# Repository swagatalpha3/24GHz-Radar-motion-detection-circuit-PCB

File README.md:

# 24GHz-Radar-motion-detection-circuit-PCB
PCB design using KiCAD

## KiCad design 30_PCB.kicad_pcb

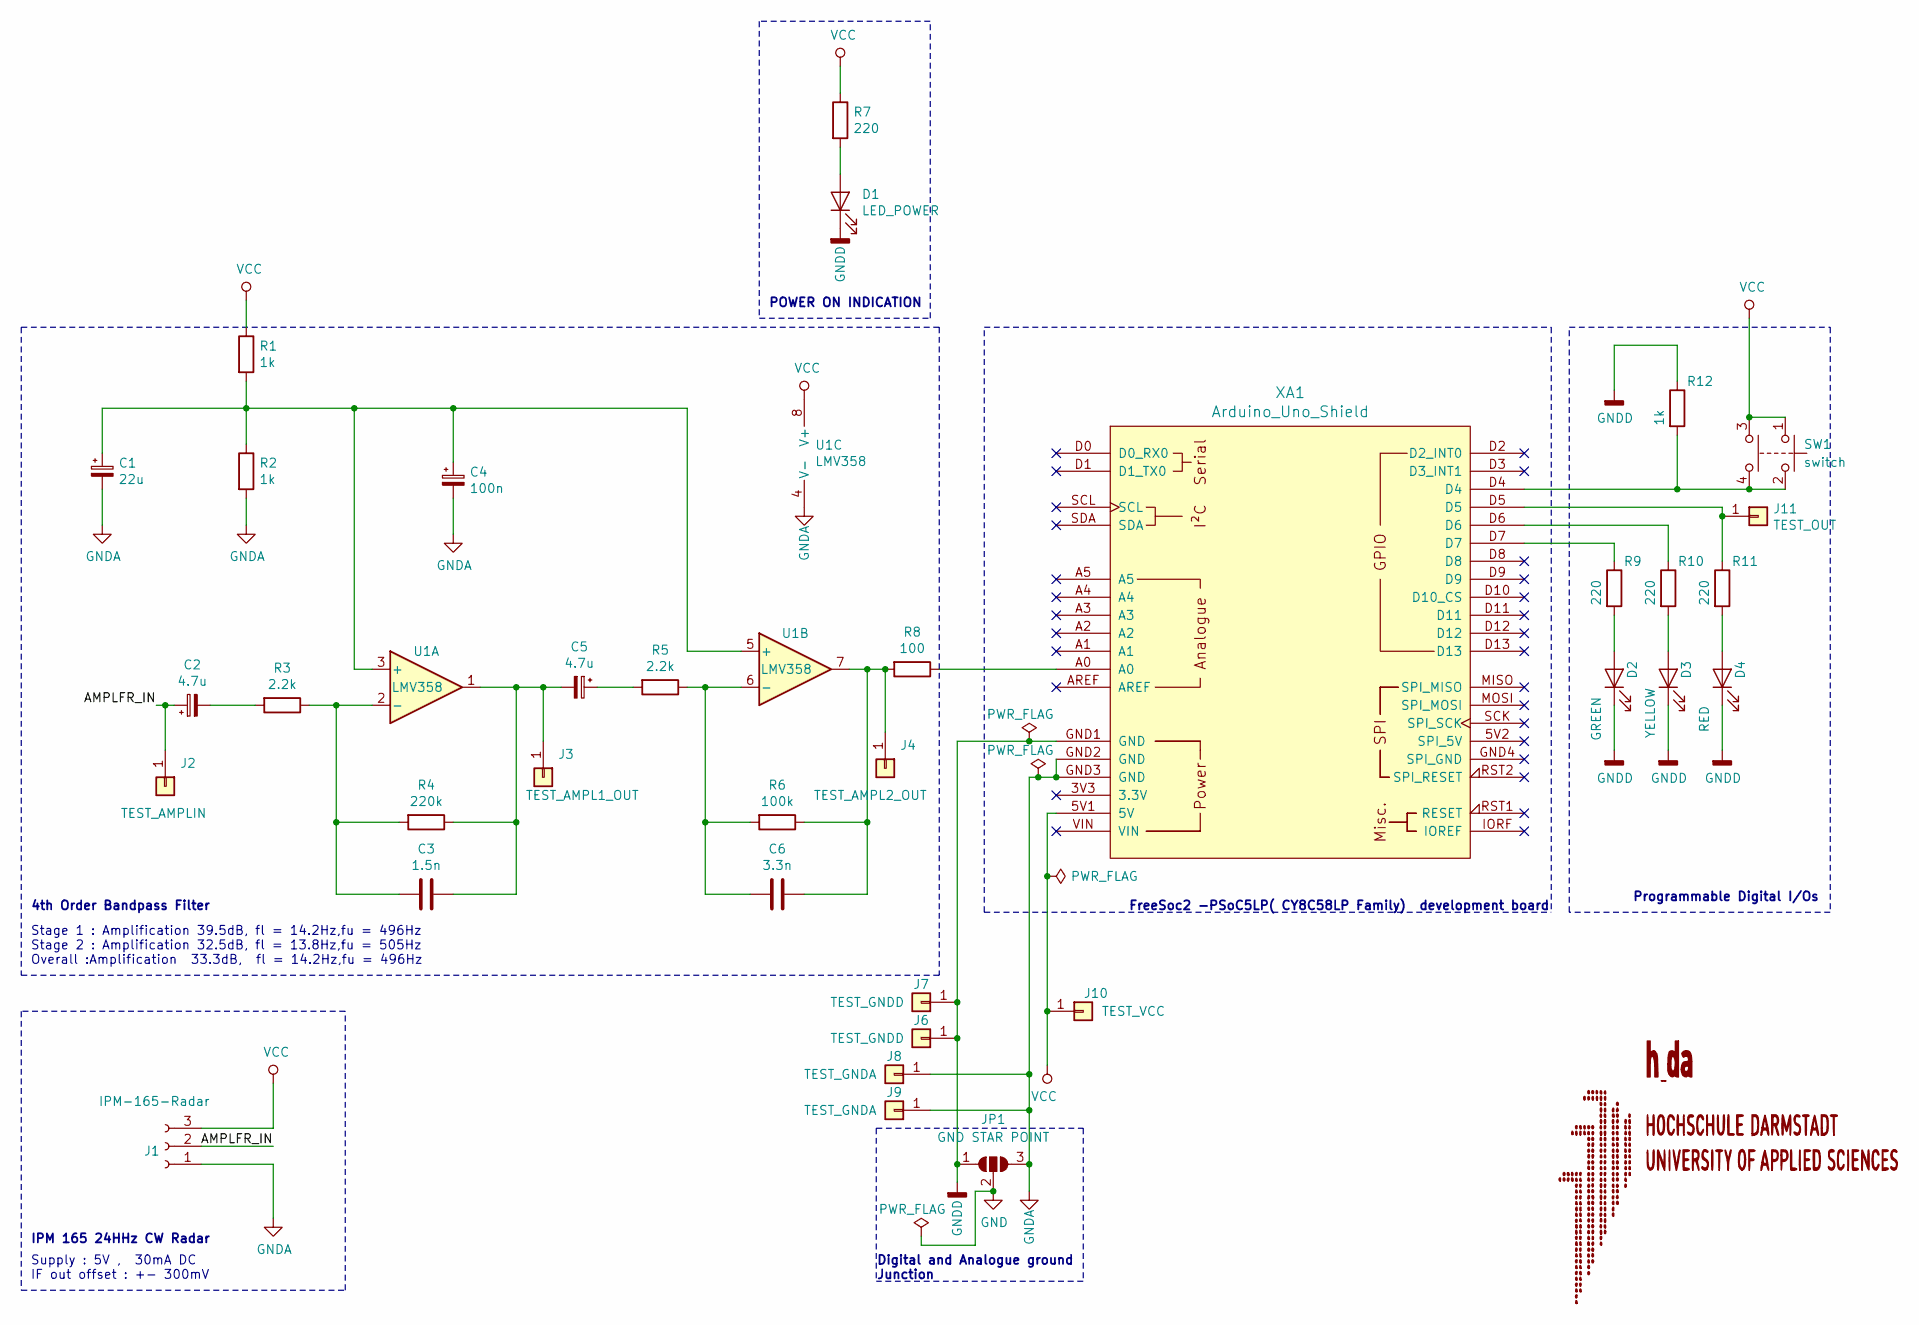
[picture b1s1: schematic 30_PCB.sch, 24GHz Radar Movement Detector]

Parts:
C1: 22u; CP_Radial_D5.0mm_P2.00mm
C2, C5: 4.7u; CP_Radial_D5.0mm_P2.00mm
C3: 1.5n; C_Rect_L7.2mm_W4.5mm_P5.00mm_FKS2_FKP2_MKS2_MKP2
C4: 100n; C_Rect_L7.2mm_W2.5mm_P5.00mm_FKS2_FKP2_MKS2_MKP2
C6: 3.3n; C_Rect_L7.2mm_W4.5mm_P5.00mm_FKS2_FKP2_MKS2_MKP2
D1: LED_POWER; D_1206_3216Metric_Pad1.42x1.75mm_HandSolder
D2: GREEN; D_1206_3216Metric_Pad1.42x1.75mm_HandSolder
D3: YELLOW; D_1206_3216Metric_Pad1.42x1.75mm_HandSolder
D4: RED; D_1206_3216Metric_Pad1.42x1.75mm_HandSolder
J1: IPM-165-Radar; PinSocket_1x03_P2.54mm_Horizontal
J2: TEST_AMPLIN; PinHeader_1x01_P1.00mm_Vertical
J3: TEST_AMPL1_OUT; PinHeader_1x01_P1.00mm_Vertical
J4: TEST_AMPL2_OUT; PinHeader_1x01_P1.00mm_Vertical
J6, J7: TEST_GNDD; PinHeader_1x01_P1.00mm_Vertical
J8, J9: TEST_GNDA; PinHeader_1x01_P1.00mm_Vertical
J10: TEST_VCC; PinHeader_1x01_P1.00mm_Vertical
J11: TEST_OUT; PinHeader_1x01_P1.00mm_Vertical
JP1: GND STAR POINT; SolderJumper-3_P1.3mm_Open_RoundedPad1.0x1.5mm
R1, R2: 1k; R_Axial_DIN0207_L6.3mm_D2.5mm_P7.62mm_Horizontal
R3, R5: 2.2k; R_Axial_DIN0207_L6.3mm_D2.5mm_P7.62mm_Horizontal
R4: 220k; R_Axial_DIN0207_L6.3mm_D2.5mm_P7.62mm_Horizontal
R6: 100k; R_Axial_DIN0207_L6.3mm_D2.5mm_P7.62mm_Horizontal
R7, R9, R10, R11: 220; R_1206_3216Metric_Pad1.42x1.75mm_HandSolder
R8: 100; R_Axial_DIN0207_L6.3mm_D2.5mm_P7.62mm_Horizontal
R12: 1k; R_1206_3216Metric_Pad1.42x1.75mm_HandSolder
SW1: switch; SW_TH_Tactile_Omron_B3F-10xx
U1: LMV358; DIP-8_W7.62mm_Socket
XA1: Arduino_Uno_Shield; Arduino_Uno_Shield_edit

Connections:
/AMPLFR_IN: C2.1, J1.2, J2.1
GND: JP1.2 (C)
GNDA: C1.2, C4.2, J1.1, J8.1, J9.1, JP1.3 (B), R2.2, U1.4 (V-), XA1.GND2 (GND), XA1.GND3 (GND)
GNDD: D1.1 (K), D2.1 (K), D3.1 (K), D4.1 (K), J6.1, J7.1, JP1.1 (A), R12.1, XA1.GND1 (GND)
unnamed: C1.1, C4.1, R1.2, R2.1, U1.3 (+), U1.5 (+)
unnamed: C2.2, R3.2
unnamed: C3.1, C5.2, J3.1, R4.1, U1.1
unnamed: C3.2, R3.1, R4.2, U1.2 (-)
unnamed: C5.1, R5.2
unnamed: C6.1, J4.1, R6.1, R8.2, U1.7
unnamed: C6.2, R5.1, R6.2, U1.6 (-)
unnamed: D1.2 (A), R7.2
unnamed: D2.2 (A), R9.2
unnamed: D3.2 (A), R10.2
unnamed: D4.2 (A), R11.2
unnamed: J11.1, R11.1, XA1.D5
unnamed: R8.1, XA1.A0
unnamed: R9.1, XA1.D7
unnamed: R10.1, XA1.D6
unnamed: R12.2, SW1.2, SW1.4, XA1.D4
VCC: J1.3, J10.1, R1.1, R7.1, SW1.1, SW1.3, U1.8 (V+), XA1.5V1 (5V)

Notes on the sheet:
4th Order Bandpass Filter
Stage 1 : Amplification 39.5dB, fl = 14.2Hz,fu = 496Hz Stage 2 : Amplification 32.5dB, fl = 13.8Hz,fu = 505Hz Overall :Amplification 33.3dB, fl = 14.2Hz,fu = 496Hz
IPM 165 24HHz CW Radar
Supply : 5V , 30mA DC IF out offset : +- 300mV
POWER ON INDICATION
FreeSoc2 -PSoC5LP( CY8C58LP Family) development board
Programmable Digital I/Os
Digital and Analogue ground Junction

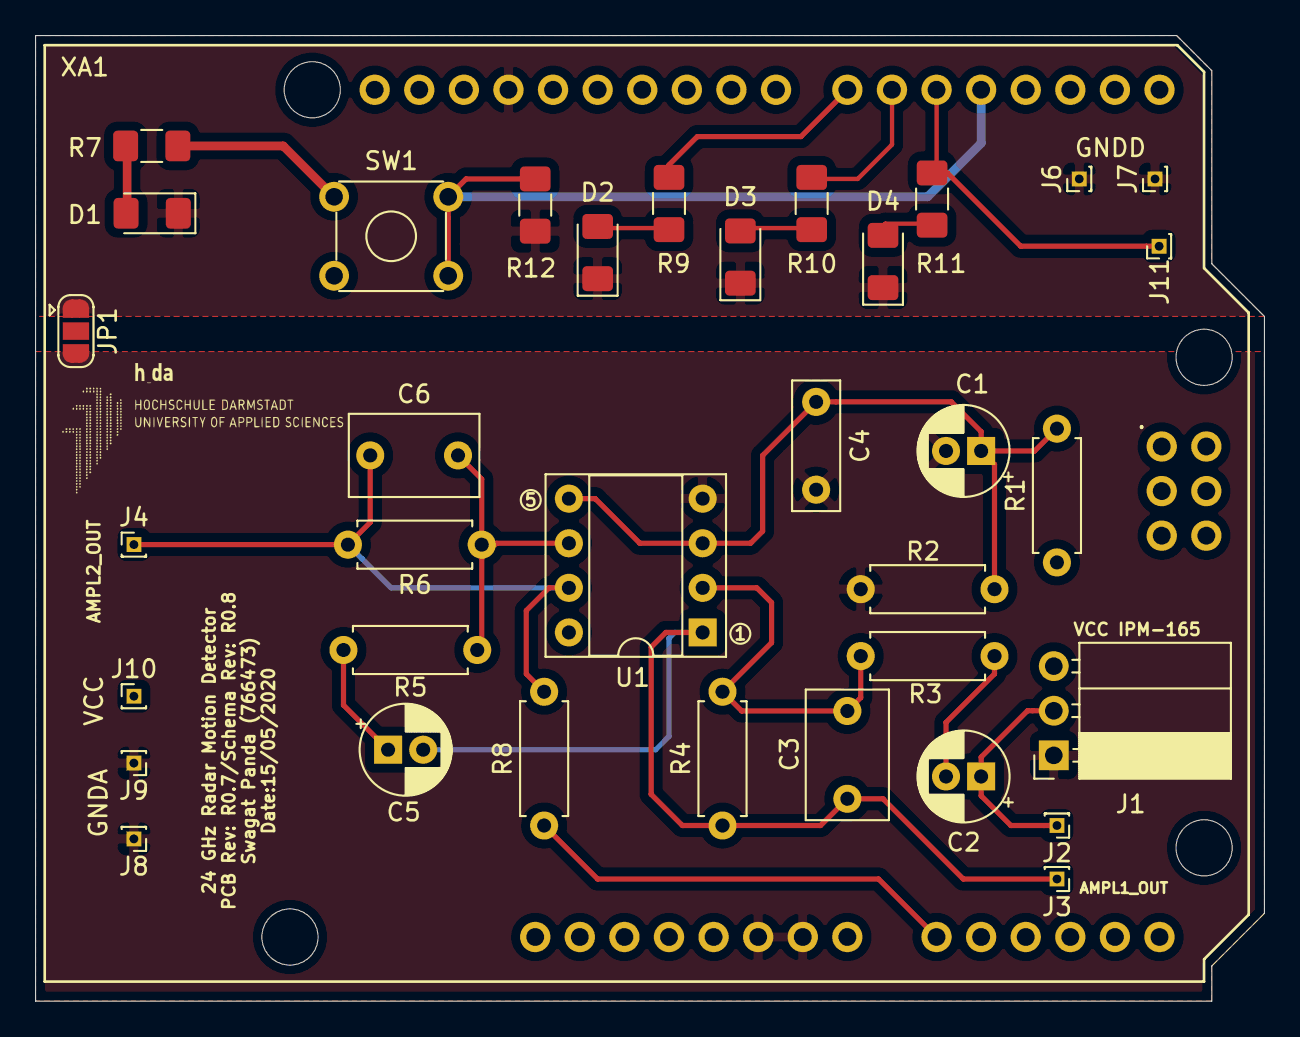
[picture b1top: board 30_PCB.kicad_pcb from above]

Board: 4 copper layers, 70.0 x 55.0 mm, 36 parts (0 on the bottom side), 20 nets.

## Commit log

2020-05-15 PCB R0.4/Schema R0.5
2020-05-16 PCB R0.5/Schema R0.6
2020-05-16 PCB R0.6/Schema R0.7--most likely final version
2020-05-16 PCB R0.7/Schema R0.8 -- Descriptions added,minor modification,Final Version
